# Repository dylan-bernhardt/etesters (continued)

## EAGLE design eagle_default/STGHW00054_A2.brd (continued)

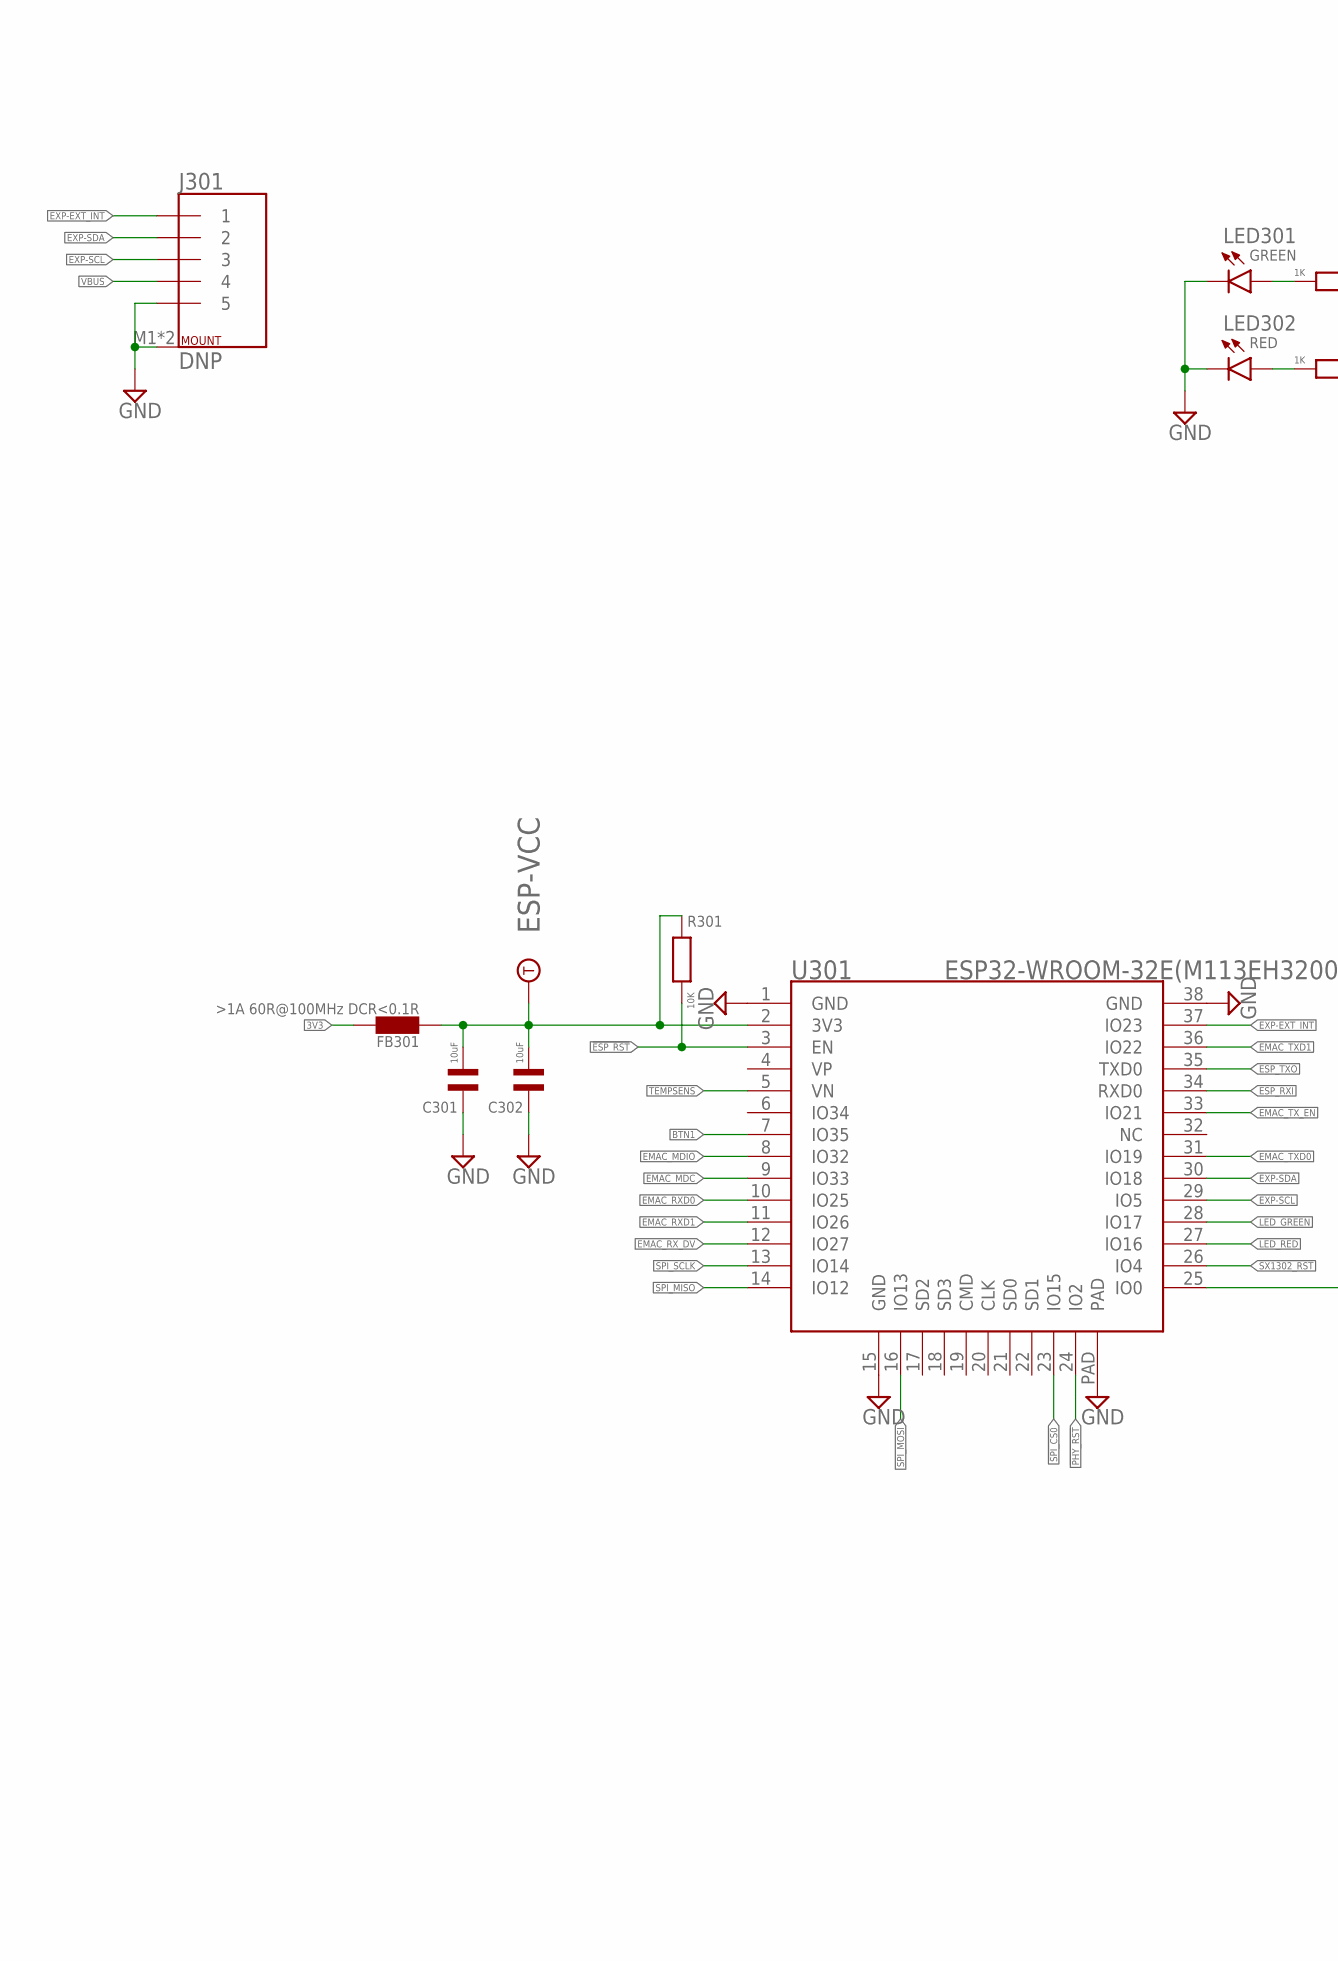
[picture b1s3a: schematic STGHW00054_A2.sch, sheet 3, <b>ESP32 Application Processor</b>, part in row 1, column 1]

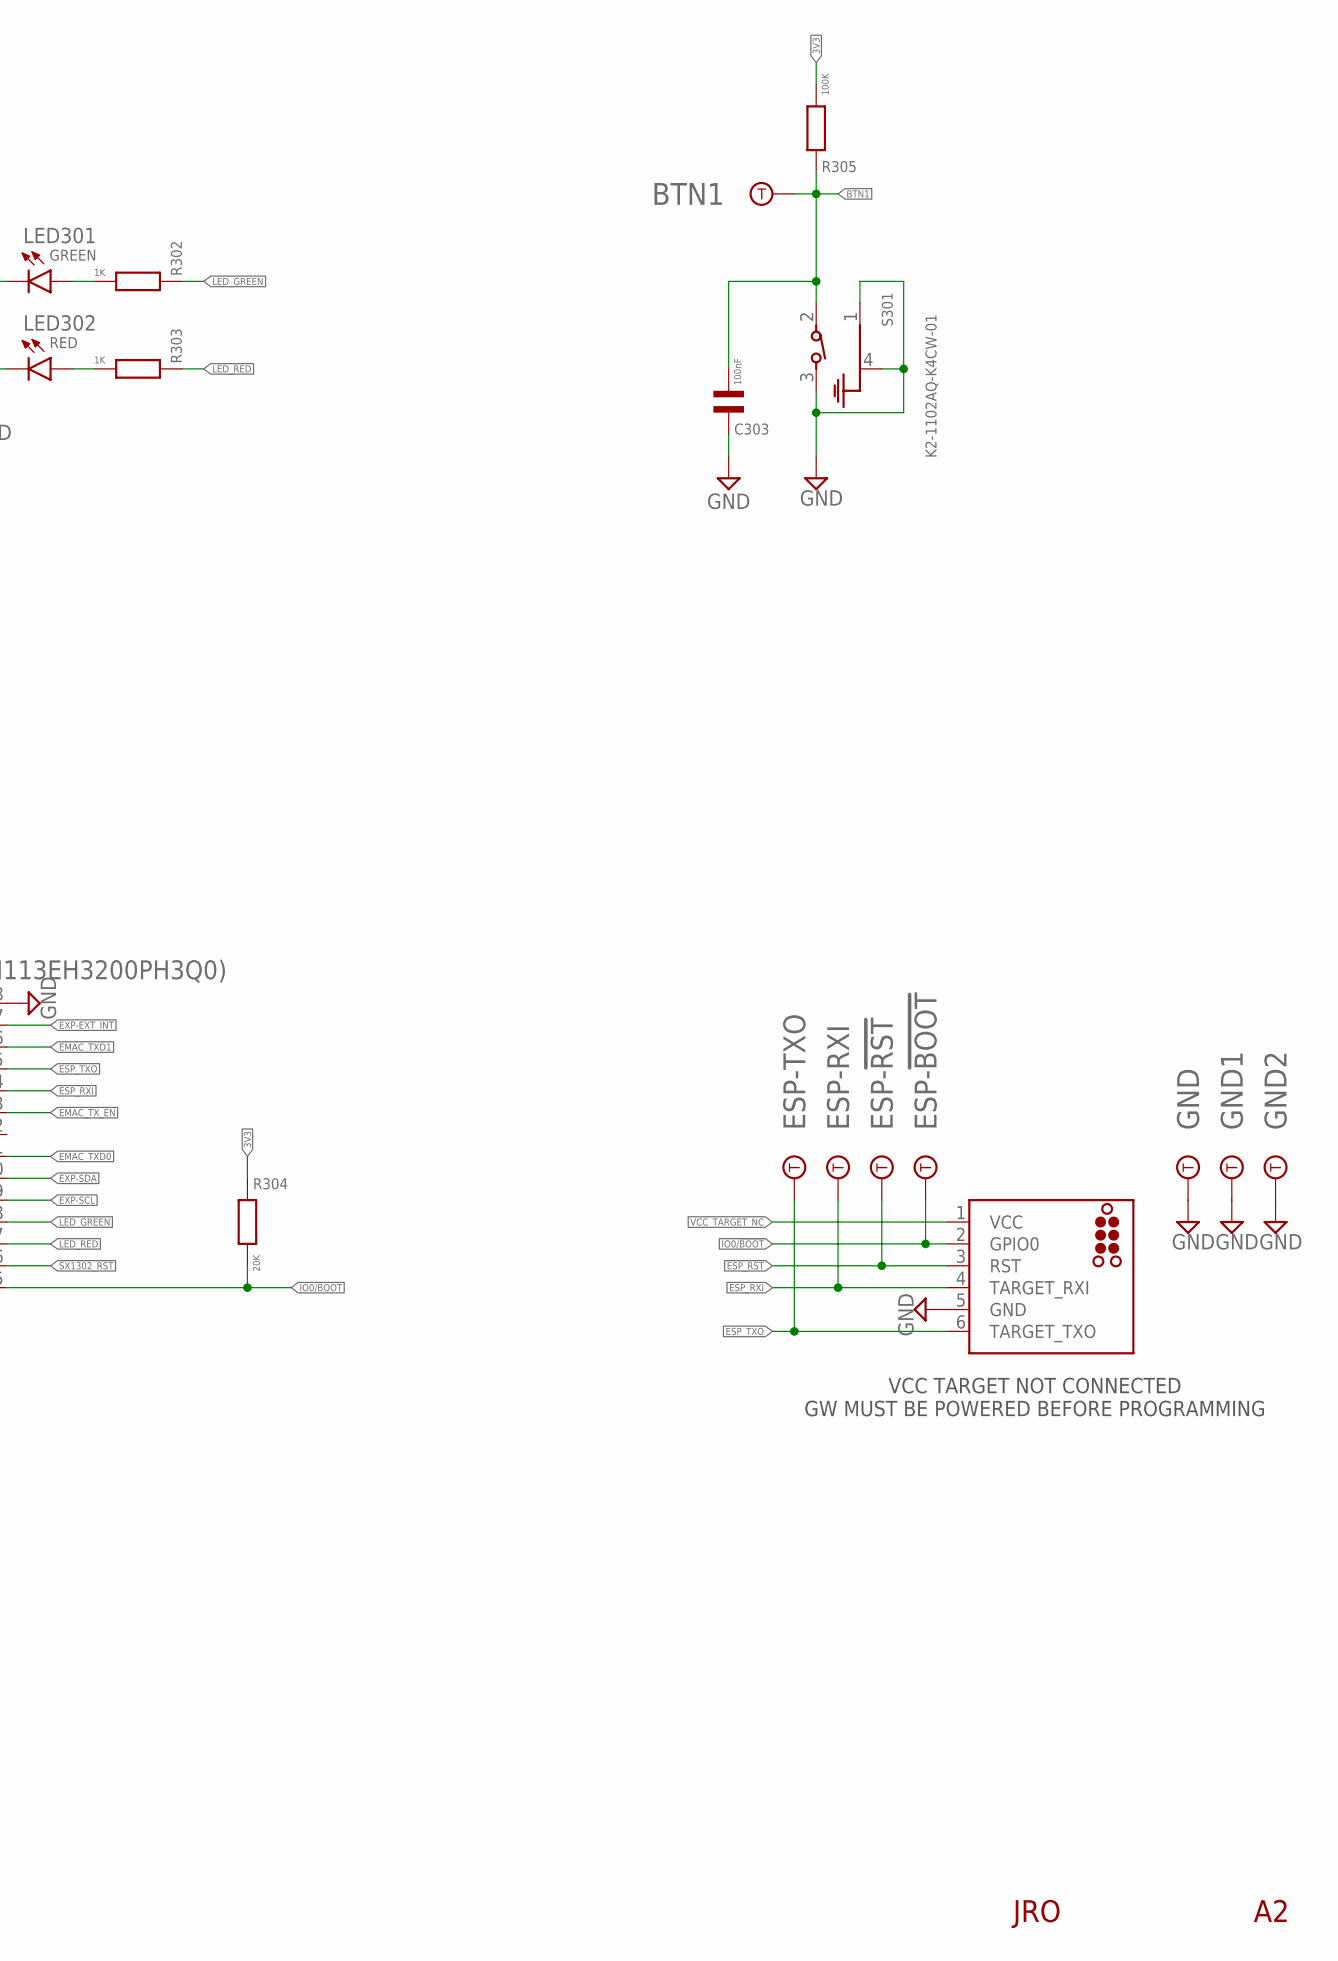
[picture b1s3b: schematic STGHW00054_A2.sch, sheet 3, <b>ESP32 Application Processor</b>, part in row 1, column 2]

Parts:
BTN1: TESPOINT-SMD1.5MM; TESTPOINT-1.5MM
C301, C302: 10uF; C0603; MPN CL10A106KP8NNNC
C303: 100nF; C0402; MPN CC0402KRX7R7BB104
ESP-!BOOT!: TESPOINT-SMD1.5MM; TESTPOINT-1.5MM
ESP-!RST!: TESPOINT-SMD1.5MM; TESTPOINT-1.5MM
ESP-RXI: TESPOINT-SMD1.5MM; TESTPOINT-1.5MM
ESP-TXO: TESPOINT-SMD1.5MM; TESTPOINT-1.5MM
ESP-VCC: TESPOINT-SMD1.5MM; TESTPOINT-1.5MM
FB301: >1A 60R@100MHz DCR<0.1R; FB0402; MPN BLM15PD600SN1D
GND, GND1, GND2: TESPOINT-SMD1.5MM; TESTPOINT-1.5MM
J301: DNP; 533980567-PICOBLADE-5P-SMT-VER; MPN C37886 (MX 1.25T-5P)
J302: TC2030-ESP-NL; TC2030-MCP-NL
LED301: GREEN; LED0603; MPN ORH-G36G
LED302: RED; LED0603; MPN ORH-R36A
R301: 10K; R0402; MPN RC0402JR-0710KL
R302, R303: 1K; R0402; MPN 0402WGF1001TCE
R304: 20K; R0402; MPN 0402WGF2002TCE
R305: 100K; R0402; MPN 0402WGF1003TCE
S301: K2-1102AQ-K4CW-01; 6MM-TH-RA
U301: ESP32-WROOM-32E(M113EH3200PH3Q0); ESP32-WROOM-32D; MPN ESP32-WROOM-32E(M113EH3200PH3Q0)

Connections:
3V3: FB301.2, R304.1, R305.2; also elsewhere on the board
3V3_ESP: C301.2, C302.2, ESP-VCC.1, FB301.1, R301.1, U301.2 (3V3)
!ESP_RST!: ESP-!RST!.1, J302.3 (RST), R301.2, U301.3 (EN); also elsewhere on the board
!PHY_RST!: U301.24 (IO2); also elsewhere on the board
!SPI_CS0!: U301.23 (IO15); also elsewhere on the board
!SX1302_RST!: U301.26 (IO4); also elsewhere on the board
BTN1: BTN1.1, C303.2, R305.1, S301.2, U301.7 (IO35)
EMAC_MDC: U301.9 (IO33); also elsewhere on the board
EMAC_MDIO: U301.8 (IO32); also elsewhere on the board
EMAC_RXD0: U301.10 (IO25); also elsewhere on the board
EMAC_RXD1: U301.11 (IO26); also elsewhere on the board
EMAC_RX_DV: U301.12 (IO27); also elsewhere on the board
EMAC_TXD0: U301.31 (IO19); also elsewhere on the board
EMAC_TXD1: U301.36 (IO22); also elsewhere on the board
EMAC_TX_EN: U301.33 (IO21); also elsewhere on the board
ESP_RXI: ESP-RXI.1, J302.4 (TARGET_RXI), U301.34 (RXD0); also elsewhere on the board
ESP_TXO: ESP-TXO.1, J302.6 (TARGET_TXO), U301.35 (TXD0); also elsewhere on the board
EXP-EXT_INT: J301.1, U301.37 (IO23)
EXP-SCL: J301.3, U301.29 (IO5)
EXP-SDA: J301.2, U301.30 (IO18)
GND: C301.1, C302.1, C303.1, GND.1, GND1.1, GND2.1, J301.5, J301.M1 (M), J301.M2 (M), J302.5 (GND), LED301.K, LED302.K, S301.1 (GND1), S301.3, S301.4 (GND), U301.1 (GND), U301.15 (GND), U301.38 (GND), U301.PAD; also elsewhere on the board
GREEN_A: LED301.A, R302.2
IO0/!BOOT!: ESP-!BOOT!.1, J302.2 (GPIO0), R304.2, U301.25 (IO0); also elsewhere on the board
LED_GREEN: R302.1, U301.28 (IO17)
LED_RED: R303.1, U301.27 (IO16)
RED_A: LED302.A, R303.2
SPI_MISO: U301.14 (IO12); also elsewhere on the board
SPI_MOSI: U301.16 (IO13); also elsewhere on the board
SPI_SCLK: U301.13 (IO14); also elsewhere on the board
TEMPSENS: U301.5 (VN); also elsewhere on the board
VBUS: J301.4; also elsewhere on the board
VCC_TARGET_NC: J302.1 (VCC)

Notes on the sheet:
VCC TARGET NOT CONNECTED GW MUST BE POWERED BEFORE PROGRAMMING
JRO

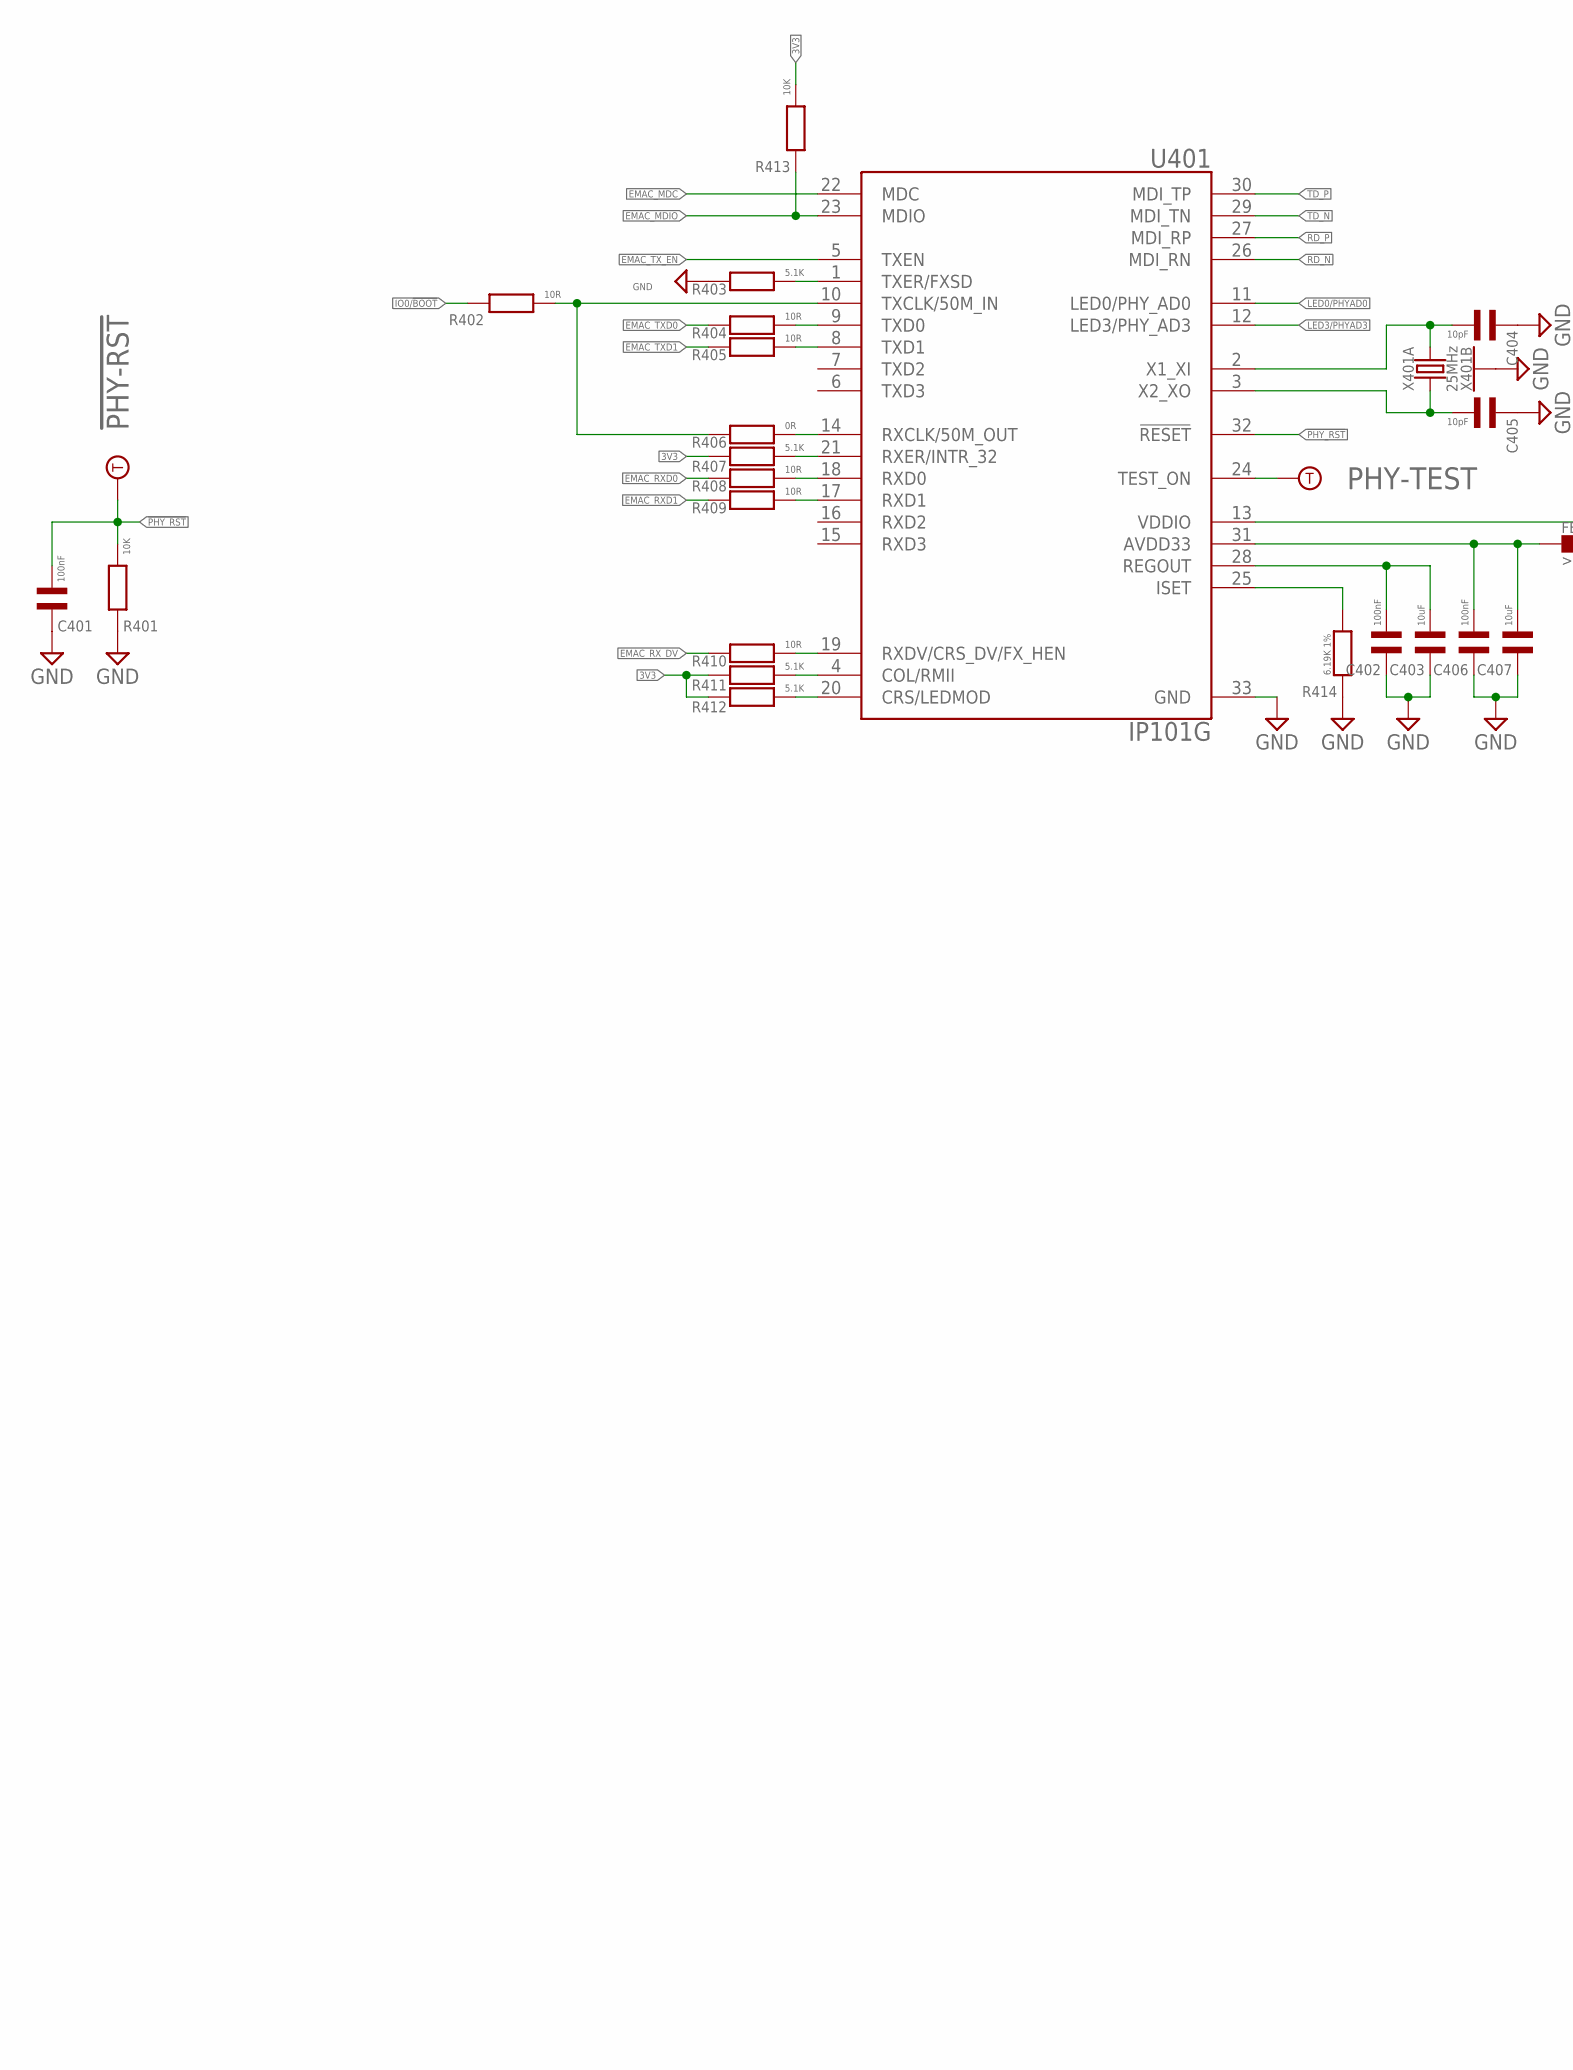
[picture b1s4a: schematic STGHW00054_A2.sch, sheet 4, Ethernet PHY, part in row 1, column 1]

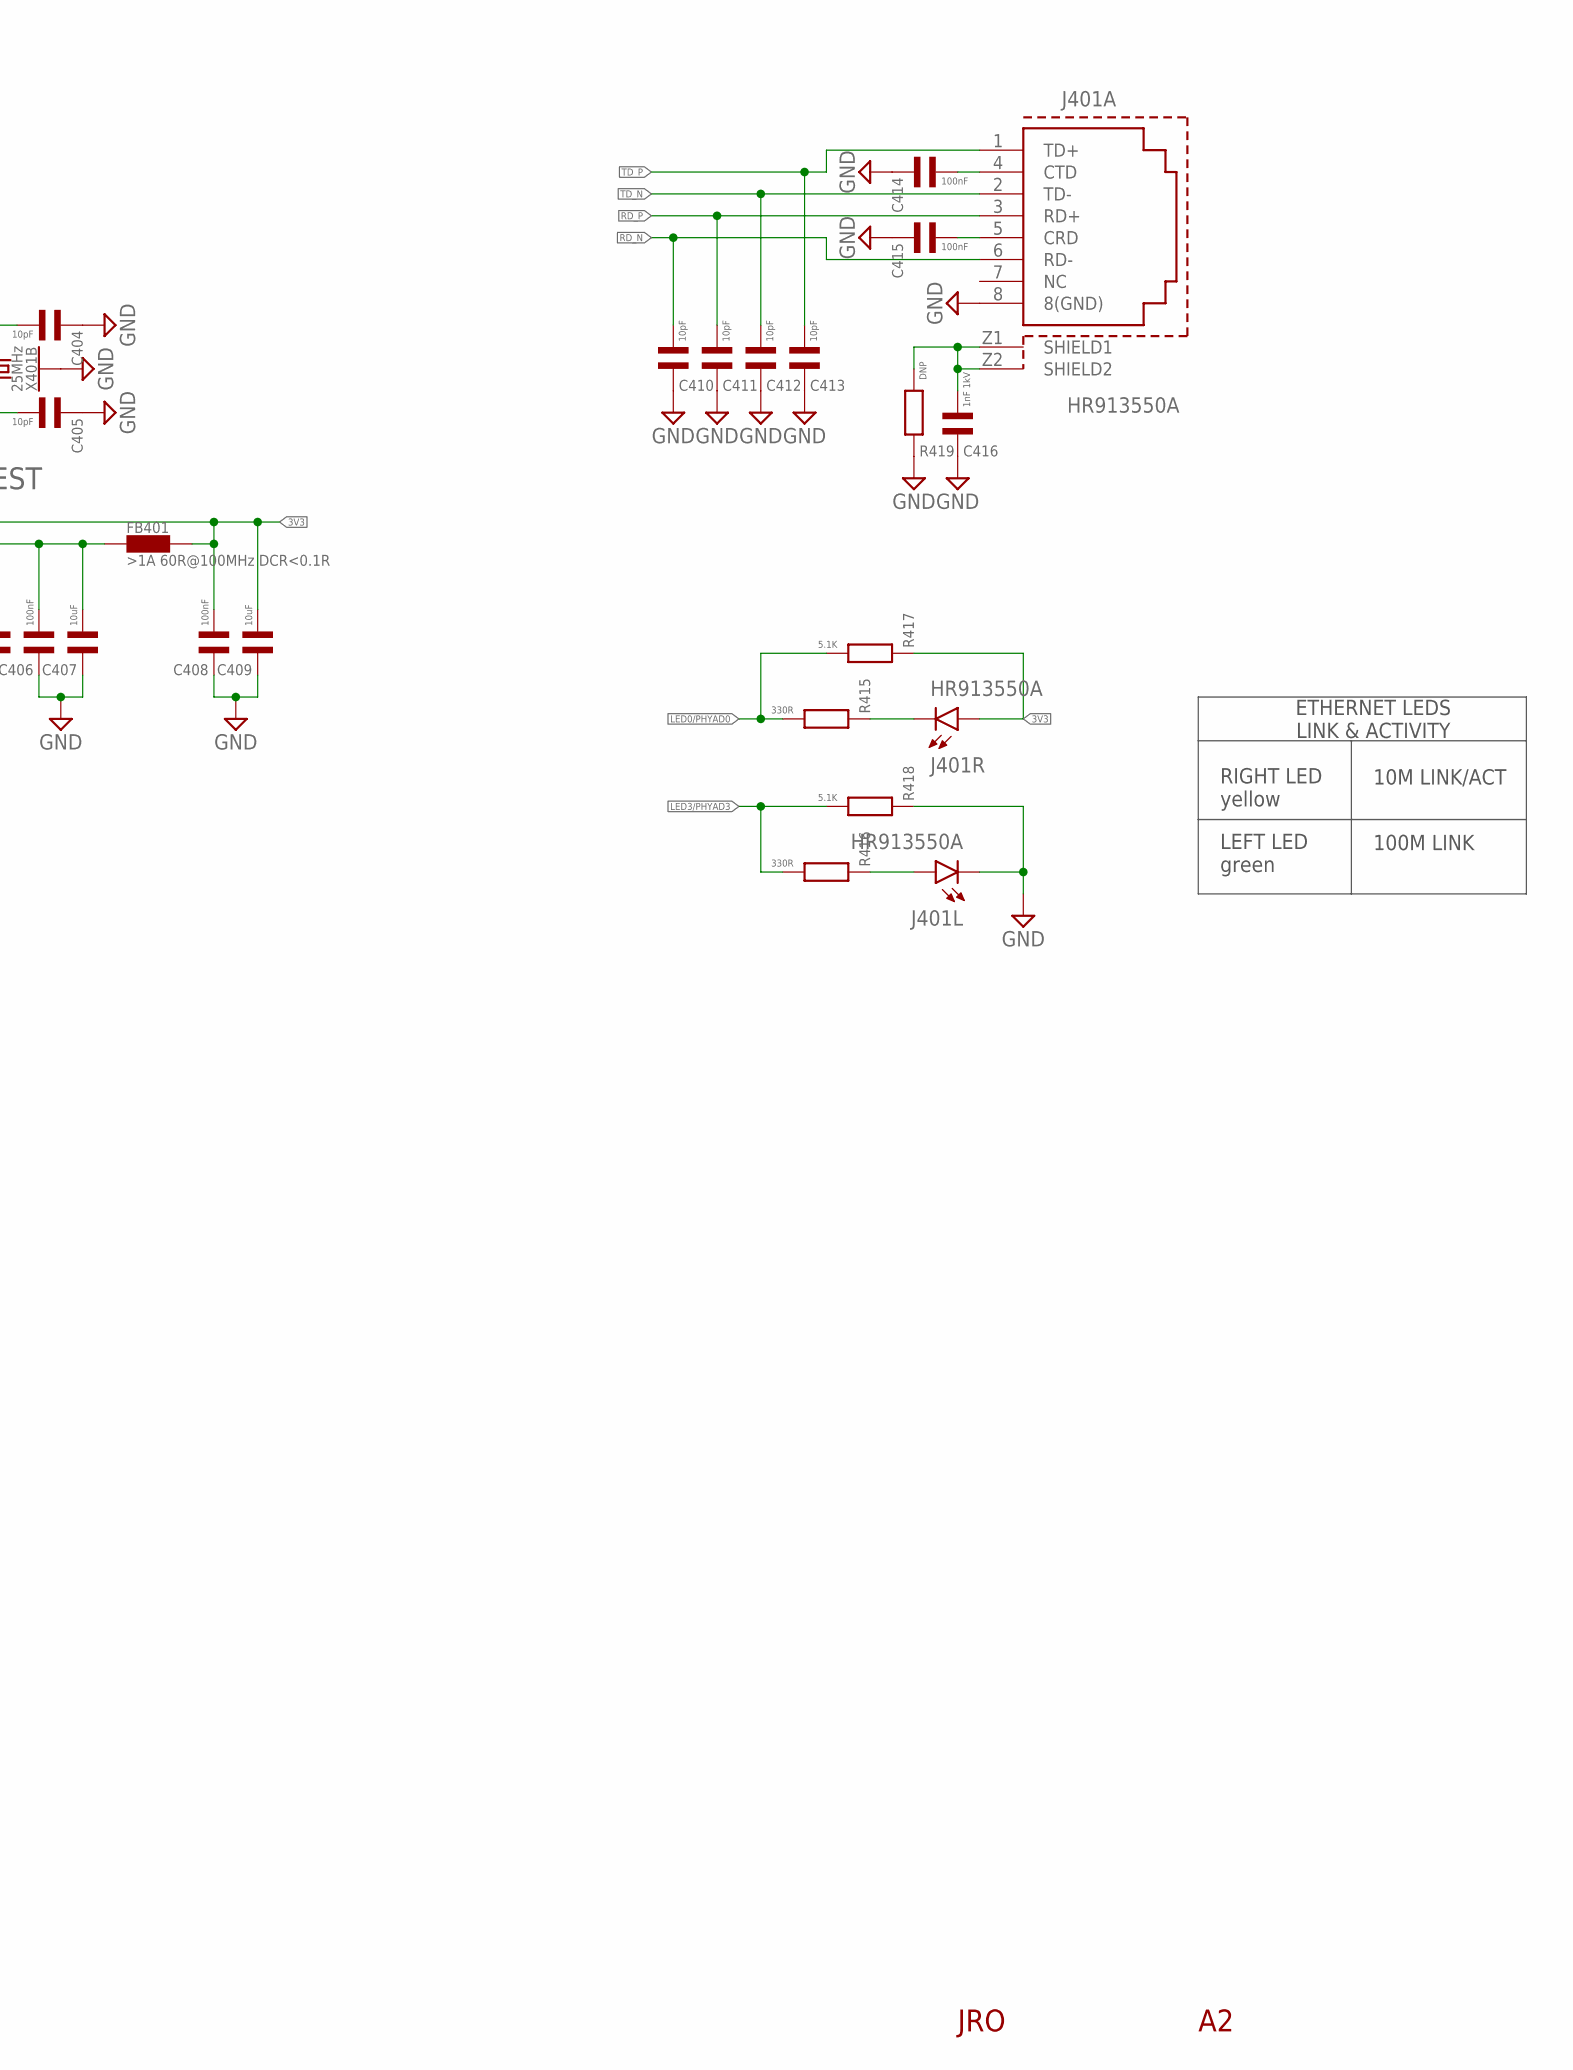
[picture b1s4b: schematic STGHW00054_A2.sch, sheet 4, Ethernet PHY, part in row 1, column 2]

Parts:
!PHY-RST!: TESPOINT-SMD1.5MM; TESTPOINT-1.5MM
C401, C402, C406, C408, C414, C415: 100nF; C0402; MPN CC0402KRX7R7BB104
C403, C407, C409: 10uF; C0603; MPN CL10A106KP8NNNC
C404, C405, C410, C411, C412, C413: 10pF; C0402; MPN CC0402JRNPO9BN100
C416: 1nF 1kV; C1206-H0.8; MPN FV31X102K102ECG
FB401: >1A 60R@100MHz DCR<0.1R; FB0402; MPN BLM15PD600SN1D
J401: HR913550A; RJ45_8P_TH_2LED; MPN-ALT 7499010441
PHY-TEST: TESPOINT-SMD1.5MM; TESTPOINT-1.5MM
R401, R413: 10K; R0402; MPN RC0402JR-0710KL
R402, R404, R405, R408, R409, R410: 10R; R0402; MPN RC0402JR-0710RL
R403, R407, R411, R412, R417, R418: 5.1K; R0402; MPN 0402WGF5101TCE
R406: 0R; R0402; MPN RC0402JR-070RL
R414: 6.19K 1%; R0402; MPN 0402WGF6191TCE
R415, R416: 330R; R0402; MPN 0402WGF3300TCE
R419: DNP; R1206; MPN WR04X0000FTL
U401: IP101G; QFN40P400X400X90-33T275N; MPN IP101GR
X401: 25MHz; OSCCC350X250X80; MPN X322525MOB4SI

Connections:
3V3: C408.2, C409.2, FB401.2, J401.11 (A), R407.2, R411.2, R412.2, R413.2, R417.1, U401.13 (VDDIO); also elsewhere on the board
100M_A: J401.9 (A), R416.1
!PHY_RST!: !PHY-RST!.1, C401.2, R401.2, U401.32 (!RESET!); also elsewhere on the board
ACT_K: J401.12 (K), R415.1
AVDD33_IP101: C406.2, C407.2, FB401.1, U401.31 (AVDD33)
COL/RMII: R411.1, U401.4 (COL/RMII)
CRS/LEDMOD: R412.1, U401.20 (CRS/LEDMOD)
EMAC_MDC: U401.22 (MDC); also elsewhere on the board
EMAC_MDIO: R413.1, U401.23 (MDIO); also elsewhere on the board
EMAC_RXD0: R408.1; also elsewhere on the board
EMAC_RXD1: R409.1; also elsewhere on the board
EMAC_RX_DV: R410.1; also elsewhere on the board
EMAC_TXD0: R404.1; also elsewhere on the board
EMAC_TXD1: R405.1; also elsewhere on the board
EMAC_TX_EN: U401.5 (TXEN); also elsewhere on the board
ETH_SHIELD: C416.2, J401.Z1 (SHIELD1), J401.Z2 (SHIELD2), R419.2
GND: C401.1, C402.1, C403.1, C404.1, C405.1, C406.1, C407.1, C408.1, C409.1, C410.1, C411.1, C412.1, C413.1, C414.1, C415.1, C416.1, J401.8 (8(GND)), J401.10 (K), R401.1, R403.1, R414.1, R418.1, R419.1, U401.33 (GND), X401.2 (1), X401.4 (1); also elsewhere on the board
IO0/!BOOT!: R402.1; also elsewhere on the board
ISET: R414.2, U401.25 (ISET)
LED0/PHYAD0: R415.2, R417.2, U401.11 (LED0/PHY_AD0)
LED3/PHYAD3: R416.2, R418.2, U401.12 (LED3/PHY_AD3)
RD_N: C410.2, J401.6 (RD-), U401.26 (MDI_RN)
RD_P: C411.2, J401.3 (RD+), U401.27 (MDI_RP)
REGOUT_IP101: C402.2, C403.2, U401.28 (REGOUT)
RJ45-CRD: C415.2, J401.5 (CRD)
RJ45-CTD: C414.2, J401.4 (CTD)
RXCLK: R406.2, U401.14 (RXCLK/50M_OUT)
RXD0: R408.2, U401.18 (RXD0)
RXD1: R409.2, U401.17 (RXD1)
RXDV: R410.2, U401.19 (RXDV/CRS_DV/FX_HEN)
RXER: R407.1, U401.21 (RXER/INTR_32)
TD_N: C412.2, J401.2 (TD-), U401.29 (MDI_TN)
TD_P: C413.2, J401.1 (TD+), U401.30 (MDI_TP)
TEST-ON_IP101: PHY-TEST.1, U401.24 (TEST_ON)
TXCLK: R402.2, R406.1, U401.10 (TXCLK/50M_IN)
TXD0: R404.2, U401.9 (TXD0)
TXD1: R405.2, U401.8 (TXD1)
TXER: R403.2, U401.1 (TXER/FXSD)
XI_IP101: C404.2, U401.2 (X1_XI), X401.3 (2)
XO_IP101: C405.2, U401.3 (X2_XO), X401.1

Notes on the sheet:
10M LINK/ACT
100M LINK
RIGHT LED yellow
LEFT LED green
ETHERNET LEDS LINK & ACTIVITY
JRO

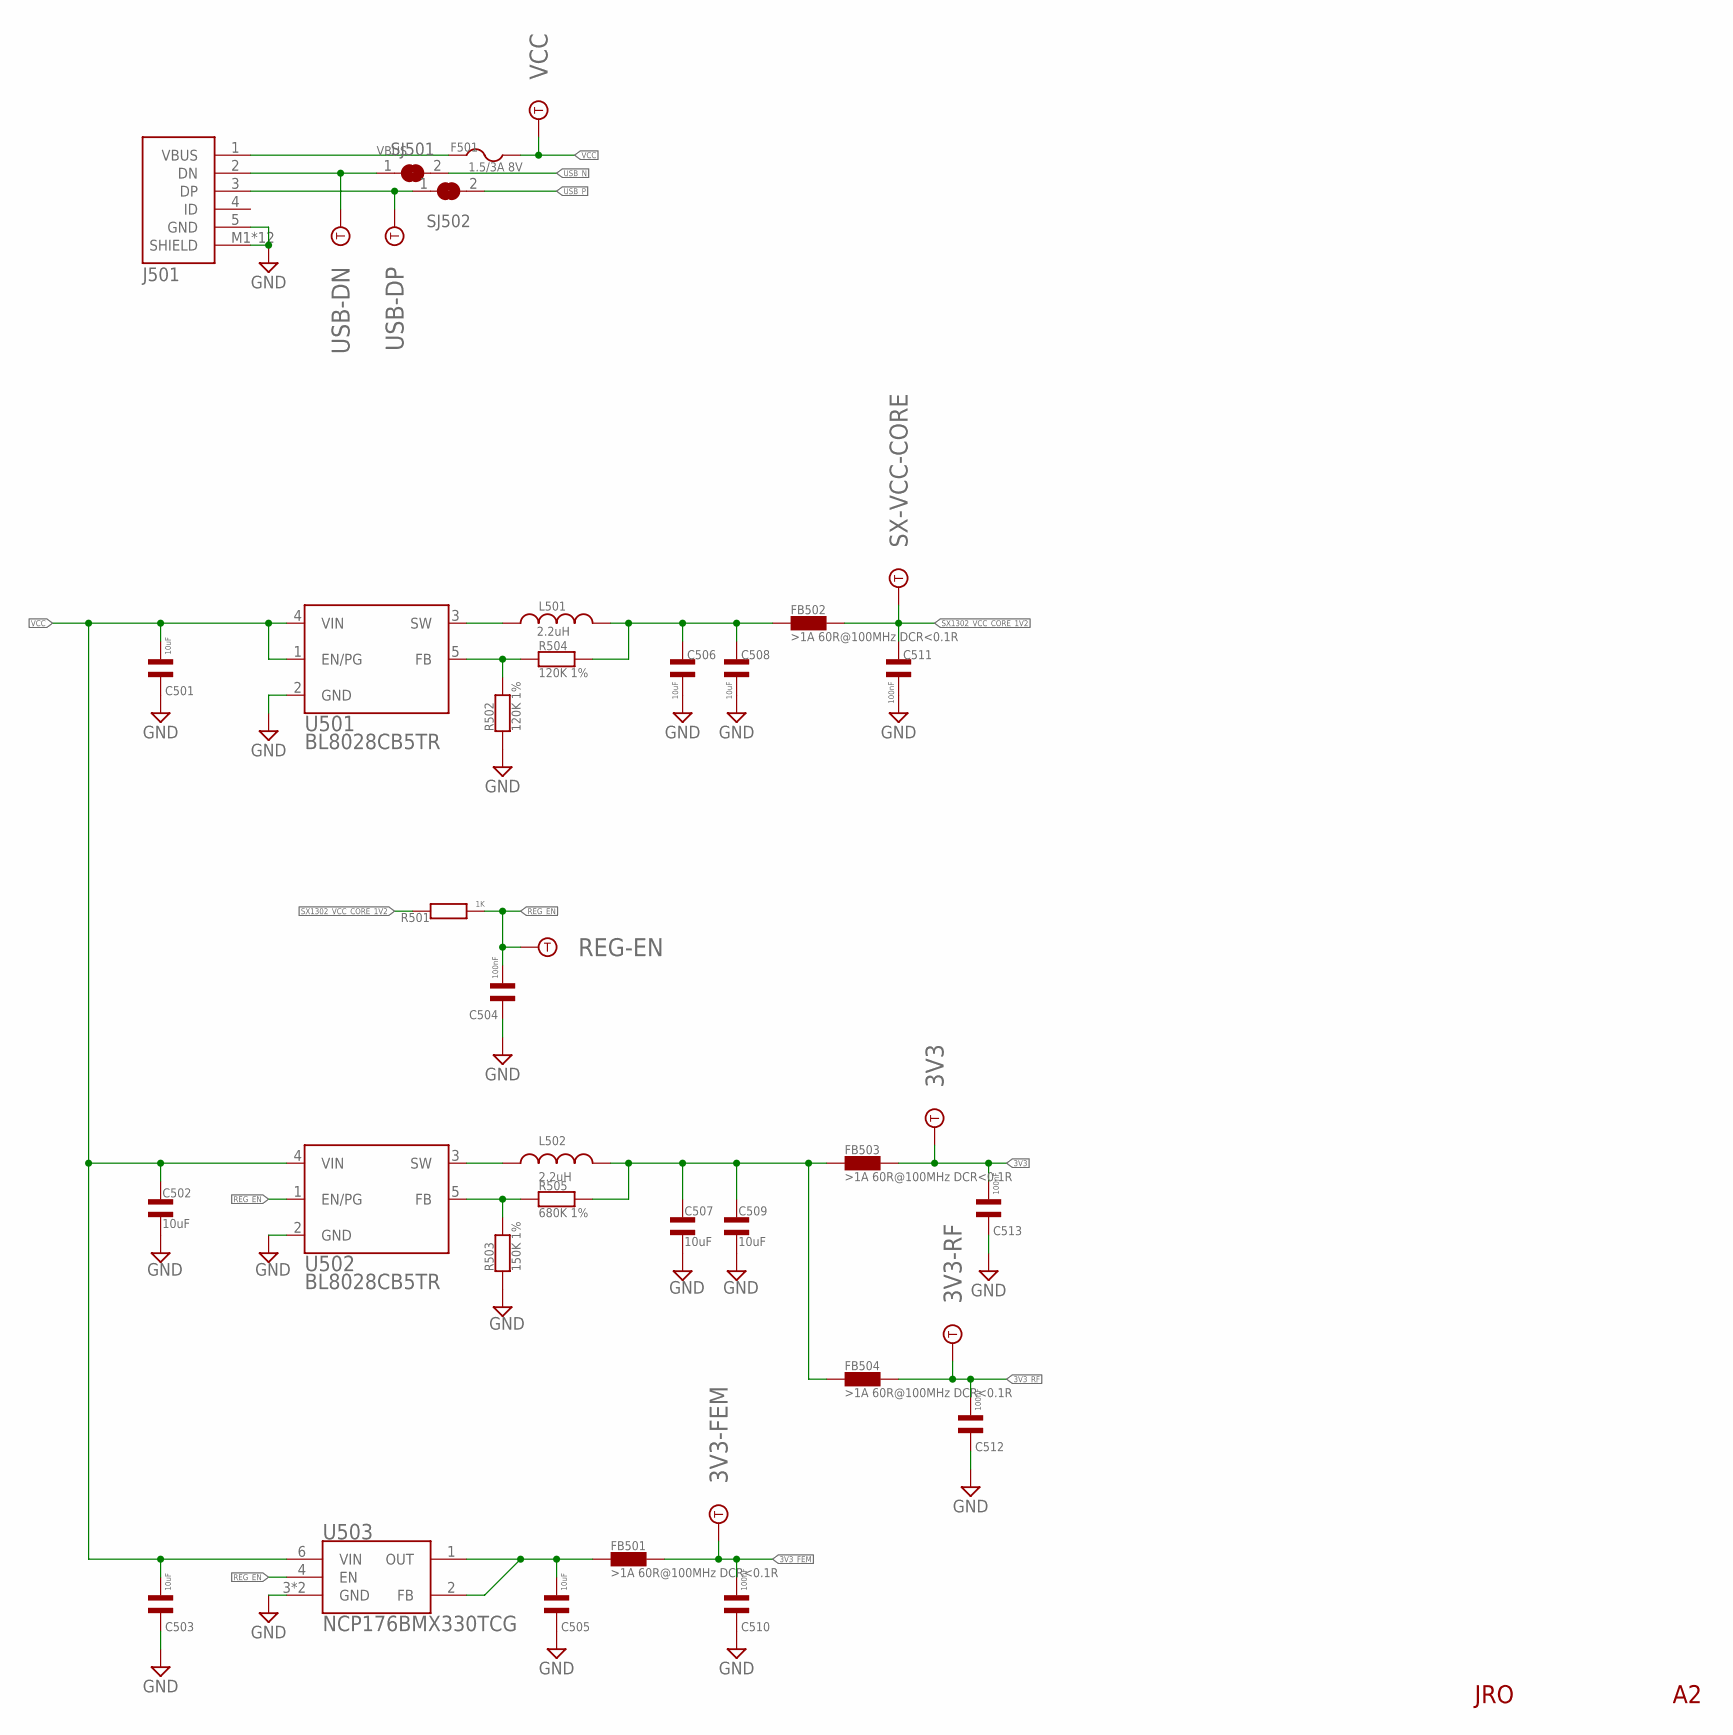
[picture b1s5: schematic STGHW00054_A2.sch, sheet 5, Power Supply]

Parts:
3V3, 3V3-FEM, 3V3-RF: TESPOINT-SMD1.5MM; TESTPOINT-1.5MM
C501, C502, C503, C505, C506, C507, C508, C509: 10uF; C0603; MPN CL10A106KP8NNNC
C504, C510, C511, C512, C513: 100nF; C0402; MPN CC0402KRX7R7BB104
F501: 1.5/3A 8V; 1210; MPN 1206L150THWR
FB501, FB502, FB503, FB504: >1A 60R@100MHz DCR<0.1R; FB0402; MPN BLM15PD600SN1D
J501: U254-051N-4BH806; USB_MICRO_3
L501, L502: 2.2uH; 1008; MPN 252012CDMCDDS-2R2MC
R501: 1K; R0402; MPN 0402WGF1001TCE
R502, R504: 120K 1%; R0402; MPN 0402WGF1203TCE
R503: 150K 1%; R0402; MPN WR04X1503FTL
R505: 680K 1%; R0402; MPN WR04X6803FTL
REG-EN: TESPOINT-SMD1.5MM; TESTPOINT-1.5MM
SJ501, SJ502: JUMPER2-NC-0603; JUMPER2-0603_NC
SX-VCC-CORE: TESPOINT-SMD1.5MM; TESTPOINT-1.5MM
U501, U502: BL8028CB5TR; SOT95P280X120-5; MPN BL8028CB5TR
U503: NCP176BMX330TCG; SON40P120X120X80-7T40X108N; MPN NCP176BMX330TCG
USB-DN: TESPOINT-SMD1.5MM; TESTPOINT-1.5MM
USB-DP: TESPOINT-SMD1.5MM; TESTPOINT-1.5MM
VCC: TESPOINT-SMD1.5MM; TESTPOINT-1.5MM

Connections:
3V3: 3V3.1, C513.2, FB503.2; also elsewhere on the board
3V3_FEM: 3V3-FEM.1, C510.2, FB501.2; also elsewhere on the board
3V3_RF: 3V3-RF.1, C512.2, FB504.2; also elsewhere on the board
DN: J501.2 (DN), SJ501.1, USB-DN.1
DP: J501.3 (DP), SJ502.1, USB-DP.1
FB_1V2: R502.2, R504.1, U501.5 (FB)
FB_3V3: R503.2, R505.1, U502.5 (FB)
GND: C501.1, C502.2, C503.1, C504.1, C505.1, C506.1, C507.2, C508.2, C509.2, C510.1, C511.1, C512.1, C513.1, J501.5 (GND), J501.M1 (SHIELD), J501.M2 (SHIELD), J501.M3 (SHIELD), J501.M4 (SHIELD), J501.MB1 (SHIELD), J501.MB2 (SHIELD), J501.MB3 (SHIELD), J501.MB4 (SHIELD), J501.MT1 (SHIELD), J501.MT2 (SHIELD), J501.MT3 (SHIELD), J501.MT4 (SHIELD), R502.1, R503.1, U501.2 (GND), U502.2 (GND), U503.3 (GND), U503.7 (GND); also elsewhere on the board
OUT_1V2: C506.2, C508.1, FB502.1, L501.2, R504.2
OUT_3V3: C507.1, C509.1, FB503.1, FB504.1, L502.2, R505.2
OUT_LDO_3V3_FEM: C505.2, FB501.1, U503.1 (OUT), U503.2 (FB)
REG_EN: C504.2, R501.2, REG-EN.1, U502.1 (EN/PG), U503.4 (EN)
SW_1V2: L501.1, U501.3 (SW)
SW_3V3: L502.1, U502.3 (SW)
SX1302_VCC_CORE_1V2: C511.2, FB502.2, R501.1, SX-VCC-CORE.1; also elsewhere on the board
USB_N: SJ501.2; also elsewhere on the board
USB_P: SJ502.2; also elsewhere on the board
VBUS: F501.1, J501.1 (VBUS); also elsewhere on the board
VCC: C501.2, C502.1, C503.2, F501.2, U501.1 (EN/PG), U501.4 (VIN), U502.4 (VIN), U503.6 (VIN), VCC.1

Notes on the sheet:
JRO
